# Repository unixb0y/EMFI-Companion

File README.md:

# EMFI ~~Pmod~~ Companion

Allows you to connect an FPGA to the rest of your EMFI setup via SMB cables. Also great for debugging your fault campaign using a logic analyzer due to breaking out all of the important signals to convenient PCB test points.

<sub>Created with KiCAD 7.0</sub>

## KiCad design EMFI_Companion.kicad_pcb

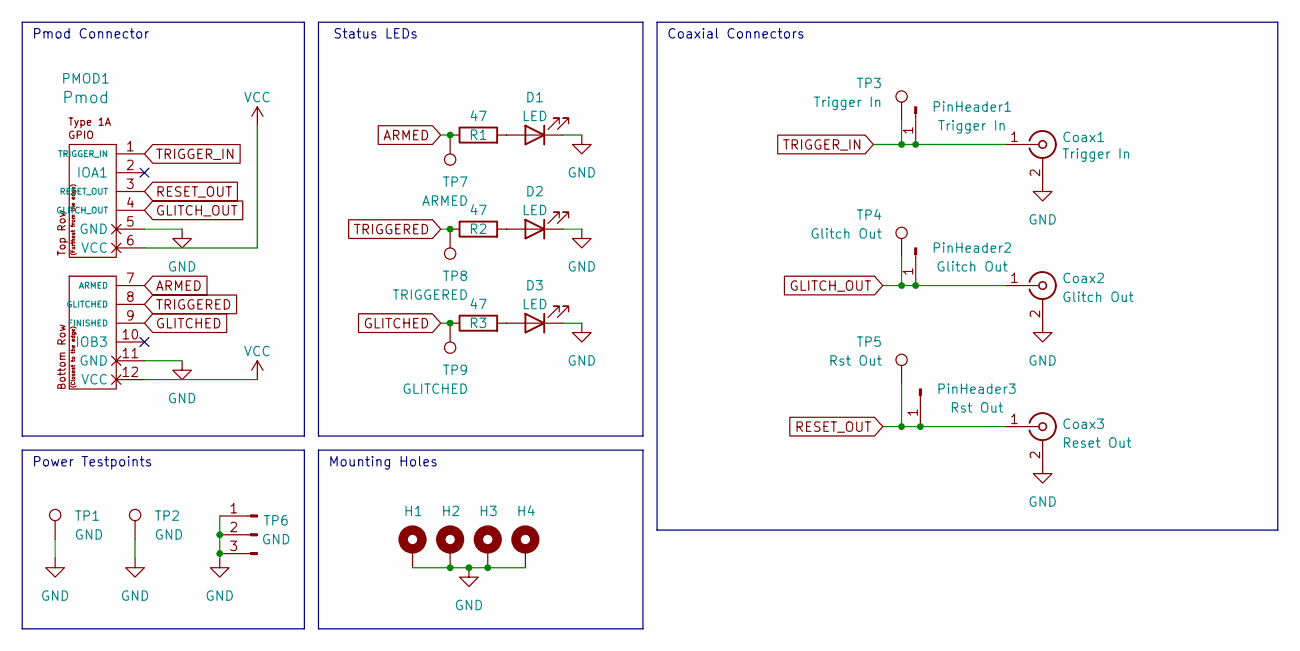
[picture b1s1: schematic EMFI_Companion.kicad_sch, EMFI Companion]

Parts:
Coax1: Trigger In; SMB_Jack_Vertical
Coax2: Glitch Out; SMB_Jack_Vertical
Coax3: Reset Out; SMB_Jack_Vertical
D1, D2, D3: LED; LED_0805_2012Metric_Pad1.15x1.40mm_HandSolder
H1: H1; MountingHole_3.2mm_M3_Pad_Via
H2: H2; MountingHole_3.2mm_M3_Pad_Via
H3: H3; MountingHole_3.2mm_M3_Pad_Via
H4: H4; MountingHole_3.2mm_M3_Pad_Via
PMOD1: PMOD-Device-x2-Type-1A-GPIO; pmod_pin_array_6x2
PinHeader1: Trigger In; PinHeader_1x01_P2.54mm_Vertical
PinHeader2: Glitch Out; PinHeader_1x01_P2.54mm_Vertical
PinHeader3: Rst Out; PinHeader_1x01_P2.54mm_Vertical
R1, R2, R3: 47; R_0805_2012Metric_Pad1.20x1.40mm_HandSolder
TP1, TP2: GND; TestPoint_Keystone_5005-5009_Compact
TP3: Trigger In; TestPoint_Keystone_5005-5009_Compact
TP4: Glitch Out; TestPoint_Keystone_5005-5009_Compact
TP5: Rst Out; TestPoint_Keystone_5005-5009_Compact
TP6: GND; PinHeader_1x03_P2.54mm_Vertical
TP7: ARMED; TestPoint_Keystone_5005-5009_Compact
TP8: TRIGGERED; TestPoint_Keystone_5005-5009_Compact
TP9: GLITCHED; TestPoint_Keystone_5005-5009_Compact

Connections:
ARMED: PMOD1.7 (ARMED), R1.1, TP7.1
GLITCHED: PMOD1.9 (FINISHED), R3.1, TP9.1
GLITCH_OUT: Coax2.1 (In), PMOD1.4 (GLITCH_OUT), PinHeader2.1, TP4.1
GND: Coax1.2 (Ext), Coax2.2 (Ext), Coax3.2 (Ext), D1.1 (K), D2.1 (K), D3.1 (K), H1.1, H2.1, H3.1, H4.1, PMOD1.5 (GND), PMOD1.11 (GND), TP1.1, TP2.1, TP6.1, TP6.2, TP6.3
unnamed: D1.2 (A), R1.2
unnamed: D2.2 (A), R2.2
unnamed: D3.2 (A), R3.2
RESET_OUT: Coax3.1 (In), PMOD1.3 (RESET_OUT), PinHeader3.1, TP5.1
TRIGGERED: PMOD1.8 (GLITCHED), R2.1, TP8.1
TRIGGER_IN: Coax1.1 (In), PMOD1.1 (TRIGGER_IN), PinHeader1.1, TP3.1
VCC: PMOD1.6 (VCC), PMOD1.12 (VCC)

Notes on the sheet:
Mounting Holes
Power Testpoints
Status LEDs
Pmod Connector
Coaxial Connectors

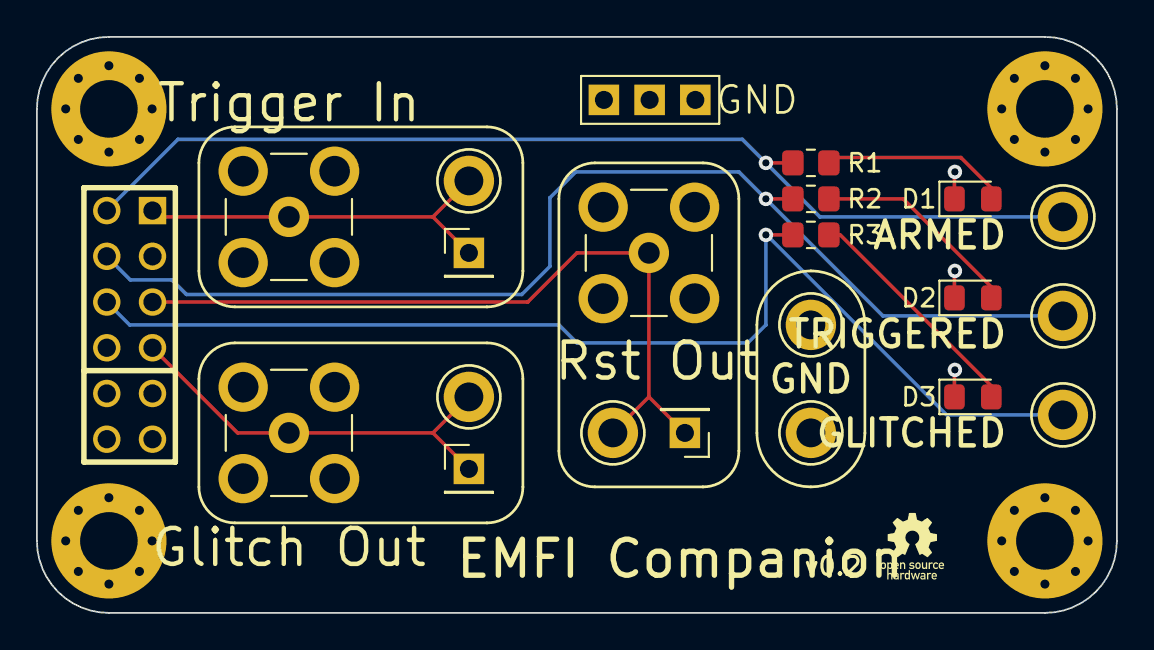
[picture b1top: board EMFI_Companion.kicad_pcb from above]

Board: 4 copper layers, 60.0 x 32.0 mm, 26 parts (0 on the bottom side), 11 nets.
